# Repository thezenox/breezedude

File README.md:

# BreezeDude
### An Open source low power FANET wind sensor.

Map of almost all wind stations: https://breezedude.de/

For more info and docs see the [Wiki](https://github.com/thezenox/breezedude/wiki)

----
<p align="center">
  <
  
   <br>
  <br>
</p>

A low cost FANET wind station using Ecowitt WS80/WS85 ultrasonic or DAVIS 6410 analog sensor.     
USB MSC Settings file and Drag&Drop Firmware upgrade. 

- wind sensor: Ecowitt WS80/WS85 or analog with reed/potentiometer (e.g. DAVIS 6410)
- pressure sensor: HP303B, BMP280, BMP3xx or SPL06-001
- LoRa module: RFM95W (SX1276), G-NiceRF SX1262, LLCC68
- antenna connector: SMA
- microcontroller: SAMD21
- connectivity: USB-C, I2C, 2x UART
- battery: 1S Li-Ion 16340 750mAh (or 1-3x 18650 external)
- solar: 5V
- PCB Size: 53x22mm

Currently using a 60x60 5V solar panel.     
Avg. power consumption at 40s send interval @3.7V battery: 1.2mA with analog sensor, 2.22mA with WS80
 
Based on SMAD21 using [adafruits samd core](https://github.com/adafruit/ArduinoCore-samd) and itsybitsy M0 variant definitions and [bootloader](https://github.com/adafruit/uf2-samdx1).     

#### Related projects and inspiration:
* https://github.com/gereic/GXAirCom
* https://github.com/jgromes/RadioLib
* https://github.com/3s1d/fanet-stm32

If you like this project

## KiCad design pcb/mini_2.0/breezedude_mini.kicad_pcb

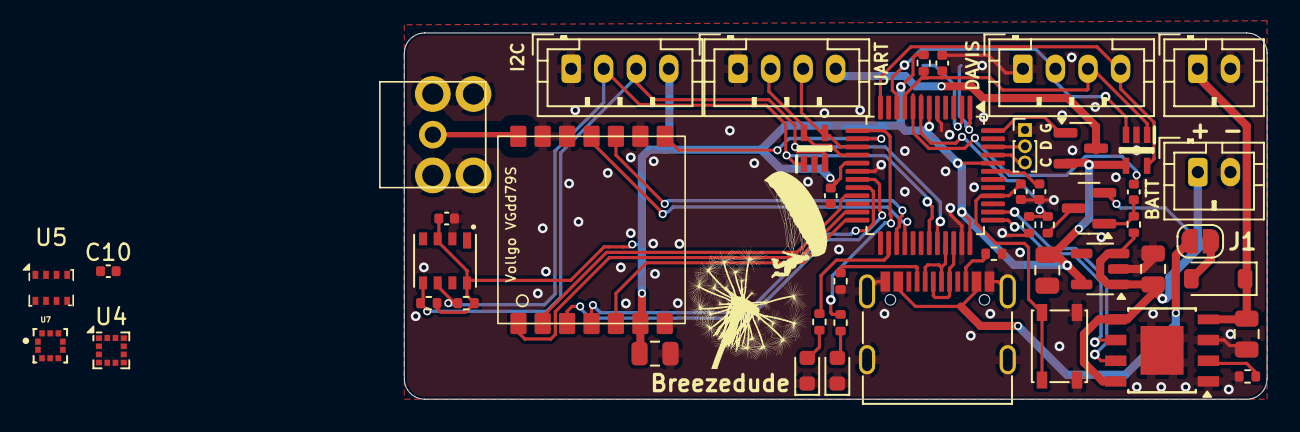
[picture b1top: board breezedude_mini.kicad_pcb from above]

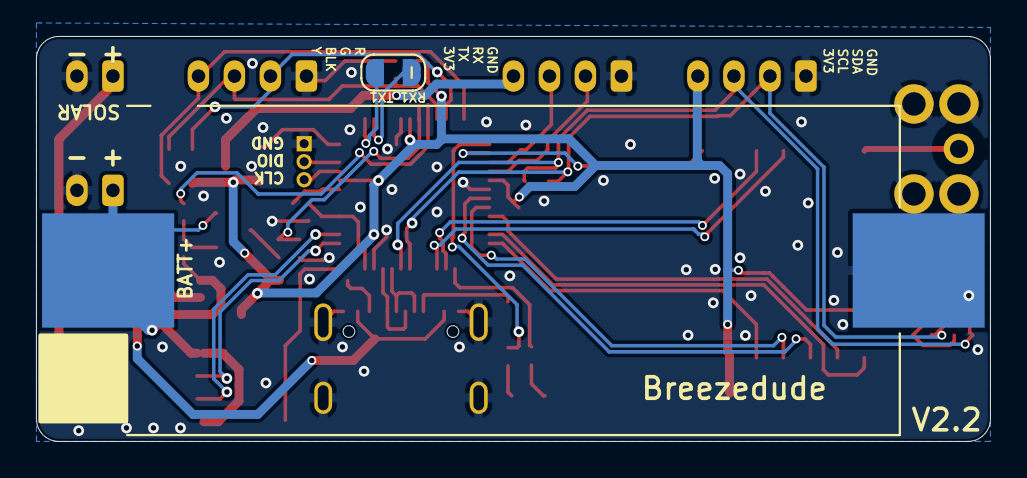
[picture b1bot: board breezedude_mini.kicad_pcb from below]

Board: 2 copper layers, 53.0 x 22.5 mm, 49 parts (2 on the bottom side), 46 nets.

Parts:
AE1: Antenna_Shield; sma_edge_6.5mm_vert
BT1: 1050; BAT_1050
C1, C3, C4, C12: 47u 6.3V; C_0805_2012Metric
C2, C6, C8: 10u 6.3V; C_0402_1005Metric
C5, C9, C11: 100n 16V; C_0402_1005Metric
C10: 220n 16V; C_0402_1005Metric
D1, D2: SMF3.3.TCT; SOT65P210X110-5N
D3: LED blue; LED_0603_1608Metric
D4: LED red; LED_0603_1608Metric
D5: Diode; D_SOD-123
J1, J6: Conn_01x02_Pin; JST_PH_B2B-PH-K_1x02_P2.00mm_Vertical
J2, J3, J5: Conn_01x04_Pin; JST_PH_B4B-PH-K_1x04_P2.00mm_Vertical
J4: Conn_01x03_Pin; PinHeader_1x03_P1.00mm_Vertical
J7: USB_C_Receptacle_USB2.0_16P; USB_C_Receptacle_G-Switch_GT-USB-7010ASV
J8: Conn_01x02_Pin; SolderJumper-2_Open_Gap1mm
JP1: SolderJumper_2_Open; SolderJumper-2_P1.3mm_Open_RoundedPad1.0x1.5mm
Q1, Q2: P-MOS; SOT-23
R1, R3: 10k; R_0402_1005Metric
R2, R5: 100k; R_0402_1005Metric
R4: 330k; R_0402_1005Metric
R6: 470; R_0402_1005Metric
R7: 200; R_0402_1005Metric
R8, R9: 3.3k; R_0402_1005Metric
R10, R11: 5.1k; R_0402_1005Metric
SW1: SW_Push; SW_SPST_PTS810
U1: PMIC-CN3063_SOIC8_; Infineon_PG-DSO-8-43
U2: STLQ015M33R; SOT-23-5
U3: ATSAMD21G18A-A; TQFP-48_7x7mm_P0.5mm
U4: LIS2MDL; LGA-12_2x2mm_P0.5mm
U5: BMP280; Bosch_LGA-8_2x2.5mm_P0.65mm_ClockwisePinNumbering
U6: vollgo_vgdd79s868n0s1
U7: BMP388; PQFN50P200X200X80-10N
U8: HP203B; HP203B-LGA8

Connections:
3V3: C4.2, C6.2, C8.2, C12.2, D1.4 (I/O4), J2.4, Q1.2 (S), R2.1, R8.2, R9.2, U2.5 (VOUT), U3.6 (VDDANA), U3.17 (VDDIO), U3.36 (VDDIO), U3.44 (VDDIN), U4.9 (Vdd), U4.10 (Vdd_IO), U5.2 (CSB), U5.6 (VDDIO), U5.8 (VDD), U6.6 (VCC), U7.1 (VDDIO), U7.6 (CSB), U7.10 (VDD), U8.3 (VDD), U8.8 (CSB)
/ANT: AE1.1 (A), U6.14 (ANT)
/BATT+: BT1.P, C3.2, J1.1, Q2.2 (S), R3.1, U1.5 (BAT), U1.8 (FB), U2.1 (VIN), U2.3 (EN)
/DAVIS_DIR: D1.3 (I/O3), J3.2, U3.10 (PA05)
/DAVIS_POWER: D1.5 (I/O2), J3.4, U3.12 (PA07)
/DAVIS_SPEED: C5.1, D1.1 (I/O1), J3.3, R2.2, U3.9 (PA04)
/LED1: R6.1, U3.26 (PA17)
/LED2: R7.1, U3.13 (PA08)
/LORA_CS: U3.24 (PA15), U6.5 (CS)
/LORA_DIO1: U3.27 (PA18), U6.10 (DIO1)
/LORA_DIO2: U3.28 (PA19), U6.11 (BUSY)
/LORA_DIO3: U3.14 (PA09), U6.8 (DIO3)
/LORA_MISO: U3.21 (PA12), U6.2 (MISO)
/LORA_MOSI: U3.19 (PB10), U6.3 (MOSI)
/LORA_RESET: U3.23 (PA14), U6.1 (RST)
/LORA_SCK: U3.20 (PB11), U6.4 (SCK)
/PV_CHARGE: U1.7 (~CHRG), U3.38 (PB23)
/PV_DONE: U1.6 (~DONE), U3.37 (PB22)
/RESET: C11.2, SW1.1, U3.40 (~RESET)
/RX: D2.5 (I/O2), J5.2, U3.16 (PA11)
/RX1: J8.2, U3.2 (PA01)
/SCL: D2.3 (I/O3), J2.3, R8.1, U3.32 (PA23), U4.1 (SCL/SPC), U5.4 (SCK), U7.2 (SCK), U8.5 (SCL)
/SDA: D2.1 (I/O1), J2.2, R9.1, U3.31 (PA22), U4.4 (SDA/SDI/SDO), U5.3 (SDI), U7.4 (SDI), U8.6 (SDA)
/SOLAR+: C1.2, D5.1 (K), J6.1, U1.4 (VIN)
/SWDCLK: J4.3, U3.45 (PA30)
/SWDIO: J4.2, U3.46 (PA31)
/TX: D2.4 (I/O4), J5.3, U3.15 (PA10)
/TX1: J8.1, U3.1 (PA00)
/USB_N: J7.A7 (D-), J7.B7 (D-), U3.33 (PA24)
/USB_P: J7.A6 (D+), J7.B6 (D+), U3.34 (PA25)
/V_DIV: R4.2, R5.1, U3.7 (PB08)
/V_IMP: C9.2, U3.8 (PB09)
GND: AE1.2 (Shield), BT1.N, C1.1, C2.1, C3.1, C4.1, C5.2, C6.1, C8.1, C10.2, C11.1, C12.1, D1.2 (GND), D2.2 (GND), D3.1 (K), D4.1 (K), J1.2, J2.1, J3.1, J4.1, J5.1, J6.2, J7.A1 (GND), J7.A12 (GND), J7.B1 (GND), J7.B12 (GND), J7.S1 (SHIELD), R1.2, R5.2, R10.2, R11.2, SW1.2, U1.1 (TEMP), U1.3 (GND), U1.9 (EP), U2.2 (GND), U3.5 (GNDANA), U3.18 (GND), U3.35 (GND), U3.42 (GND), U4.6 (GND), U4.8 (GND), U5.1 (GND), U5.7 (GND), U6.7 (GND), U6.9 (GND), U6.12 (GND), U6.13 (GND), U7.3 (VSS), U7.5 (SDO), U7.8 (VSS), U7.9 (VSS), U8.2 (GND)
unnamed: D3.2 (A), R6.2
unnamed: D4.2 (A), R7.2
unnamed: D5.2 (A), JP1.2 (B)
unnamed: J7.A5 (CC1), R10.1
unnamed: J7.B5 (CC2), R11.1
unnamed: J7.A4 (VBUS), J7.A9 (VBUS), J7.B4 (VBUS), J7.B9 (VBUS), JP1.1 (A)
unnamed: Q2.3 (D), R4.1
unnamed: C9.1, Q2.1 (G), R3.2
unnamed: R1.1, U1.2 (ISET)
unnamed: C2.2, U3.43 (VDDCORE)
unnamed: C10.1, U4.5 (C1)
SW_WS: Q1.1 (G), U3.48 (PB03)
VCC_WS: J5.4, Q1.3 (D)

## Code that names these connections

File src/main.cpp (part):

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// 1 { PORTA, 10, PIO_SERCOM, (PIN_ATTR_DIGITAL), No_ADC_Channel, NOT_ON_PWM, NOT_ON_TIMER, EXTERNAL_INT_10 }, // TX: SERCOM0/PAD[2]

// SERCOM 4 - SPI RFM95W LoRa
#define PIN_LORA_MISO MISO  // 28 PA12  - SERCOM2/PAD[0] | alt SERCOM4/PAD[0]
#define PIN_LORA_MOSI MOSI  // 29 PB10  -                | alt SERCOM4/PAD[2]
#define PIN_LORA_SCK SCK    // 30 PB11  -                | alt SERCOM4/PAD[3]

#define PIN_LORA_CS 5    // PA15 - SERCOM2/PAD[3] | alt SERCOM4/PAD[3]
#define PIN_LORA_RESET 2 // PA14 - SERCOM2/PAD[2] | alt SERCOM4/PAD[2]
#define PIN_LORA_DIO0 11 // PA16 - SERCOM1/PAD[0] | alt SERCOM3/PAD[0]
#define PIN_LORA_DIO1 10 // PA18 - SERCOM1/PAD[2] | alt SERCOM3/PAD[2]
#define PIN_LORA_DIO2 12 // PA19 - SERCOM1/PAD[3] | alt SERCOM3/PAD[3]
#define PIN_LORA_DIO3 3  // PA09 - SERCOM0/PAD[1], ADC
#define PIN_PV_CHARGE 38// PB23
#define PIN_PV_DONE 37 // PB22
#define PIN_PS_WS 36 // PB03 PIO_SERCOM_ALT, PIN_ATTR_NONE, No_ADC_Channel, NOT_ON_PWM, NOT_ON_TIMER, EXTERNAL_INT_NONE },  // SPI Flash MISO on ItsyBitsy M0, Power switch control for WSXX Sensor. HW >= 2.2

#define PIN_SERCOM1_TX 40 // PA00 SERCOM1 PAD0
#define PIN_SERCOM1_RX 10 // PA01 SERCOM1 PAD1

// Pins with solder jumpers 
#define PIN_ID0 6 // PA20 - SERCOM5/PAD[2]
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#ifdef HAS_HEATER
  #define HEATER_MAX_V 9.20 // Maximum setpoint voltage, thermal limit by inductor (~1,8A conntiniuos, actual voltage ~8V)
  #define PIN_EN_DCDC 19 // A5 19 PB02
  #define PIN_EN_HEATER 4 //D4/A8 PA08
#endif


#define PIN_DAVIS_SPEED 17 // A3 17 PA04
#define PIN_DAVIS_DIR 18 // A4 18 PA05
#define PIN_DAVIS_POWER 9 // 9 PA07 - power for direction potentiometer. Turn off if not used to save power

// SERCOM 3 - I²C Barometer / Digipot
#define PIN_SDA 26 // PA22
#define PIN_SCL 27 // PA23

// I2C Barometer
BMP280 bmp280; // Bosch BMP280
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// Yellow - Pot supply voltage

// SERCOM 0 - uart serial Sensor/ GPS / Debug
#define PIN_RX 0 // A6 PA11
#define PIN_TX 1 // A7 PA10

#define PIN_STATUSLED 13 // PA17 // blue, 1.2mA @ 2.77V = 470Ohm
#define PIN_ERRORLED 4 //D4/A8 PA08 // red 2.9mA @ 2.16V = 390Ohm
#define PIN_V_READ_TRIGGER A2 // D16 PB09
#define PIN_V_READ A1 // D15 PB08 - { PORTB,  8, PIO_ANALOG, (PIN_ATTR_PWM|PIN_ATTR_TIMER), ADC_Channel2, PWM4_CH0, TC4_CH0, EXTERNAL_INT_8 }, // ADC/AIN[2]

#define VERSIONFILE (char*) "version.txt"
#define SETTINGSFILE (char*) "settings.txt"
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
#define LORA_SYNCWORD 0xF1 //SX1262: 0xF4 0x14 https://blog.classycode.com/lora-sync-word-compatibility-between-sx127x-and-sx126x-460324d1787a is handled by RadioLib

SX1276 radio_sx1276 = new Module(PIN_LORA_CS, PIN_LORA_DIO0, PIN_LORA_RESET, PIN_LORA_DIO1);
SX1262 radio_sx1262 = new Module(PIN_LORA_CS, PIN_LORA_DIO1, PIN_LORA_RESET, PIN_LORA_DIO2);
LLCC68 radio_llcc68 = new Module(PIN_LORA_CS, PIN_LORA_DIO1, PIN_LORA_RESET, PIN_LORA_DIO2);

PhysicalLayer* radio_phy = nullptr;
bool transmittedFlag = false;
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
// read status pins of solar charger
void get_solar_charger_state(){
  pinMode(PIN_PV_CHARGE, INPUT_PULLUP);
  pinMode(PIN_PV_DONE, INPUT_PULLUP);
  pv_done = !digitalRead(PIN_PV_DONE);
  pv_charging = !digitalRead(PIN_PV_CHARGE);
  pinDisable(PIN_PV_CHARGE);
  pinDisable(PIN_PV_DONE);
}

// Trigger ADC and calc battery value in percent and volts
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int read_wind_dir(){
  int val = 0;
  analogReference(AR_DEFAULT); //3.3V refernece
  pinMode(PIN_DAVIS_DIR, INPUT);
  pinMode(PIN_DAVIS_POWER,OUTPUT);
  digitalWrite(PIN_DAVIS_POWER,1);

int d = analogRead(PIN_DAVIS_DIR);


if(is_davis6410){
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  val = (int)(360.0/1023.0 * (float)d);
}
 // ... other analog sensors
digitalWrite(PIN_DAVIS_POWER,0);
pinDisable(PIN_DAVIS_POWER);
pinDisable(PIN_DAVIS_DIR);
return val;
}

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    wdt_disable();
  }

// Using TC4 for hardware pulsecounting on Falling edge on pin PA04 (D17). No interrupts needed.
  if(!undervoltage && is_davis6410){ // pulse counting anemometer
    actual_sleep = rtc_sleep_cfg(time_to_sleep);
    setup_pulse_counter(); // need to setup GCLK6 before
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
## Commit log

2024-02-26 init
2024-03-03 include altitude in FANET name broadcast
2024-03-14 fix name
2024-04-11 fix whitespace in name, add support for SPL06 barometer
2024-04-12 continuous sampling of ws80 while in deepsleep. added short term wind history for averaging and better gust tracking
2024-06-01 added images
2024-06-01 add pictures and basic infos
2024-06-01 add flashing instruction for factory new samd21
2024-12-27 mini V2.0
2025-01-03 v2.1. fixed p-fet, added vollgo cc68, vertical SMA
2025-01-28 0.4. moved to radiolib, added some debugging features, more baro supported, added I2C display
2025-02-08 improved WS85/85 data reading + autodetection
2025-02-14 add mini v2 picture
2025-05-04 mini V2.2
2025-05-04 LICENSE.txt
2025-05-06 add support for HP203B pressure sensor
2025-06-06 Update README.md
    add link to wiki
2025-06-12 add bootloader & firmware binaries
